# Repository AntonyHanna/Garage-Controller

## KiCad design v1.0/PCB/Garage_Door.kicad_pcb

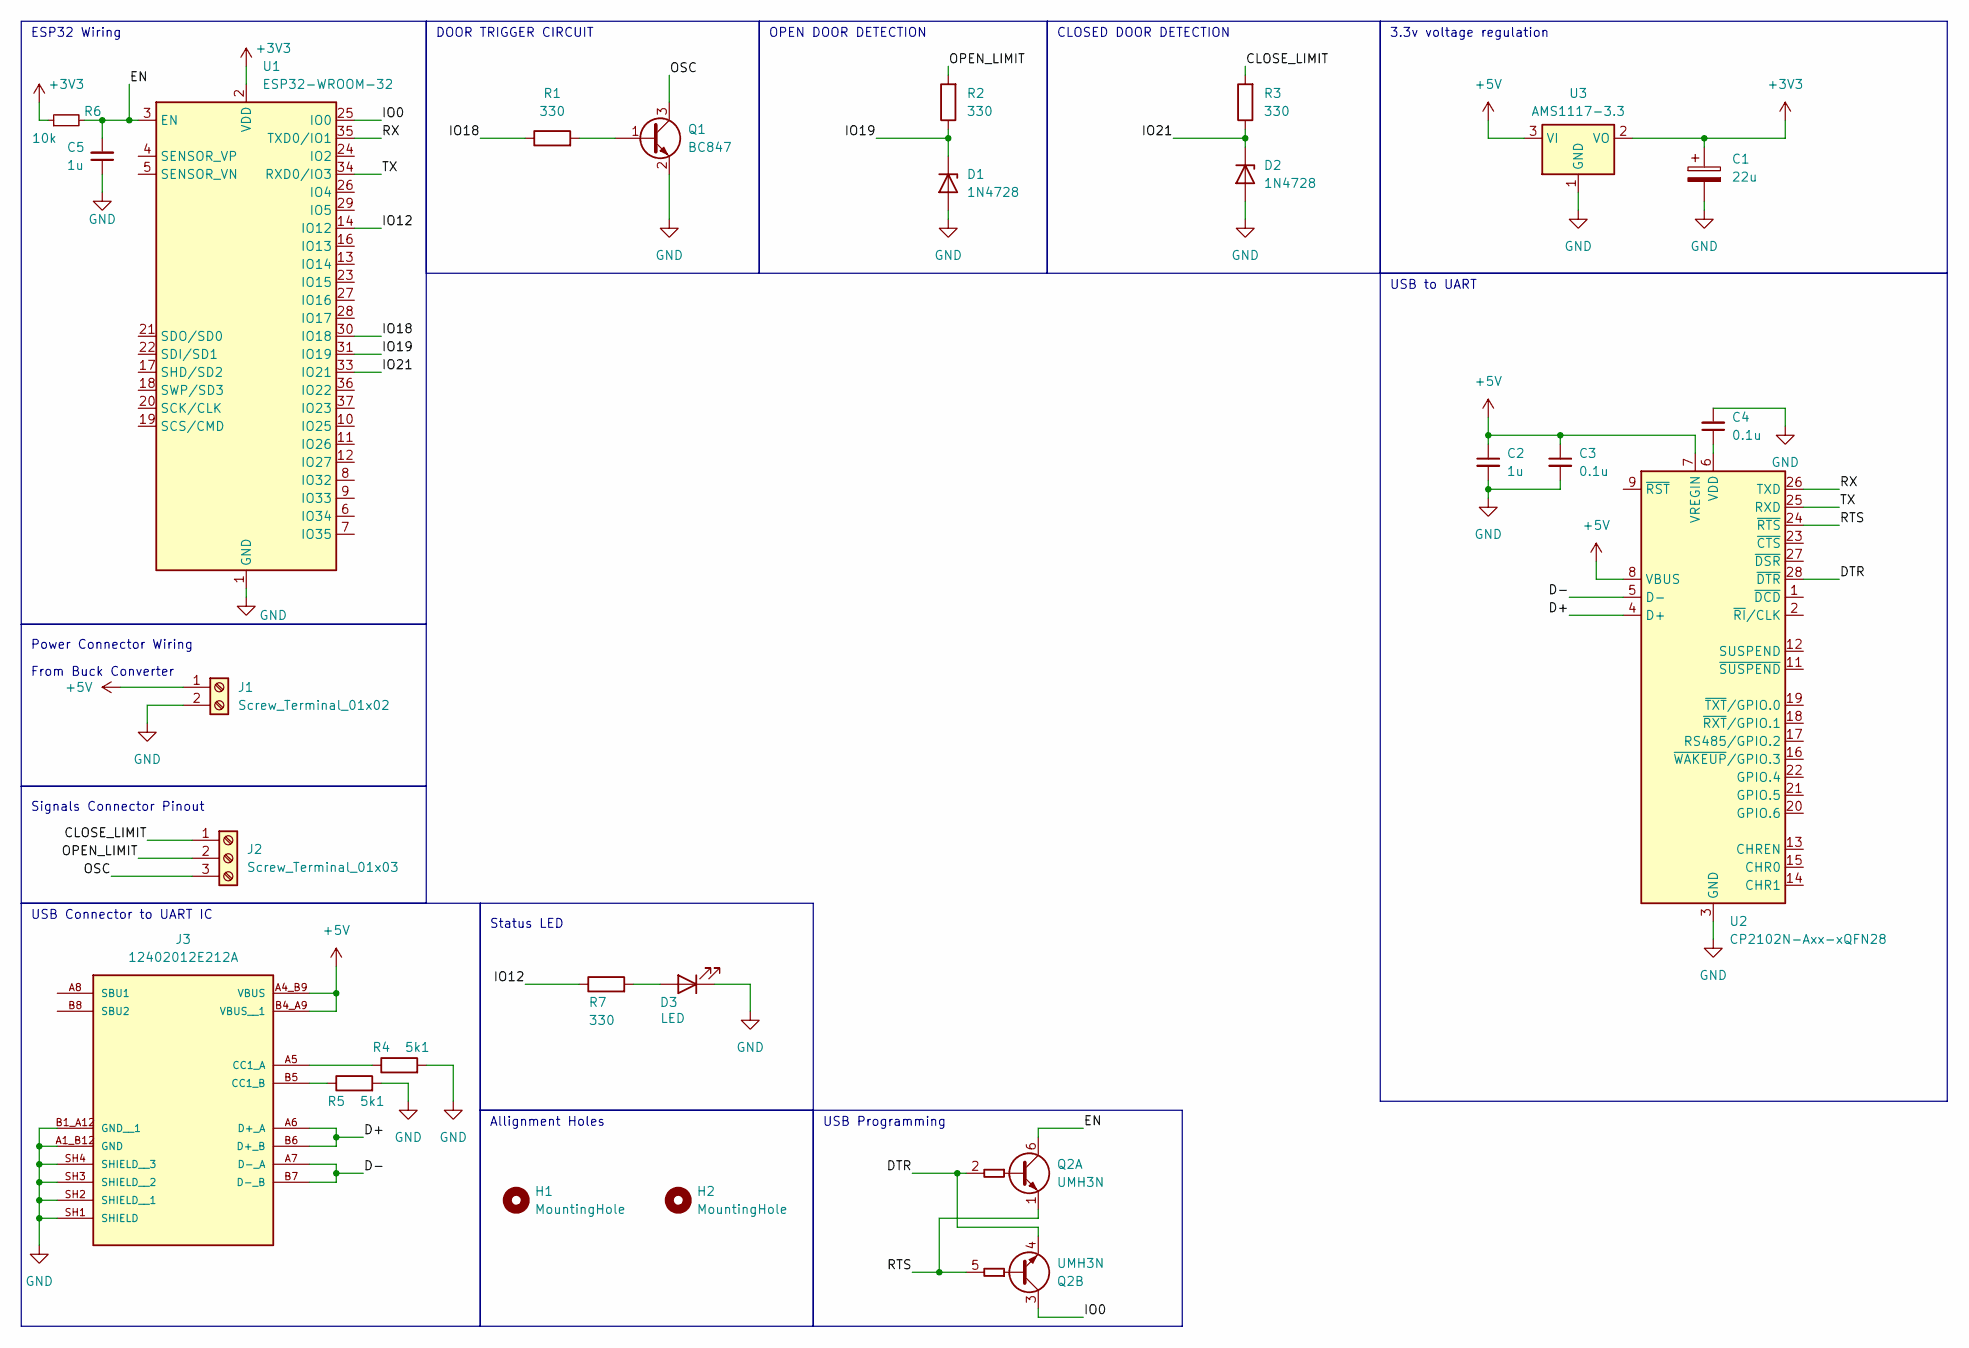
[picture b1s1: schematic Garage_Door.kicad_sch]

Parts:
C1: 22u; C_0603_1608Metric_Pad1.08x0.95mm_HandSolder
C2, C5: 1u; C_0603_1608Metric_Pad1.08x0.95mm_HandSolder
C3, C4: 0.1u; C_0603_1608Metric_Pad1.08x0.95mm_HandSolder
D1, D2: 1N4728; D_SOD-323F
D3: LED; LED_0603_1608Metric_Pad1.05x0.95mm_HandSolder
H1, H2: MountingHole; MountingHole_2.5mm
J1: Screw_Terminal_01x02; TerminalBlock_Phoenix_MKDS-1,5-2-5.08_1x02_P5.08mm_Horizont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
J2: Screw_Terminal_01x03; TerminalBlock_Phoenix_MKDS-1,5-3-5.08_1x03_P5.08mm_Horizont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
J3: 12402012E212A; AMPHENOL_12402012E212A; PARTREV 4
Q1: BC847; SOT-23
Q2: UMH3N; SOT-363_SC-70-6
R1, R2, R3, R7: 330; R_0603_1608Metric_Pad0.98x0.95mm_HandSolder
R4, R5: 5k1; R_0603_1608Metric_Pad0.98x0.95mm_HandSolder
R6: 10k; R_0603_1608Metric_Pad0.98x0.95mm_HandSolder
U1: ESP32-WROOM-32
U2: CP2102N-Axx-xQFN28; QFN-28-1EP_5x5mm_P0.5mm_EP3.35x3.35mm
U3: AMS1117-3.3; SOT-223-3_TabPin2

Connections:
+3V3: C1.1, R6.1, U1.2 (VDD), U3.2 (VO)
+5V: C2.1, C3.1, J1.1, J3.A4_B9 (VBUS), J3.B4_A9 (VBUS__1), U2.7 (VREGIN), U2.8 (VBUS), U3.3 (VI)
/CLOSE_LIMIT: J2.1, R3.2
/D+: J3.A6 (D+_A), J3.B6 (D+_B), U2.4 (D+)
/D-: J3.A7 (D-_A), J3.B7 (D-_B), U2.5 (D-)
/DTR: Q2.2 (B1), Q2.4 (E2), U2.28 (~DTR)
/EN: C5.2, Q2.6 (C1), R6.2, U1.3 (EN)
/IO0: Q2.3 (C2), U1.25 (IO0)
/IO12: R7.1, U1.14 (IO12)
/IO18: R1.1, U1.30 (IO18)
/IO19: D1.1 (K), R2.1, U1.31 (IO19)
/IO21: D2.1 (K), R3.1, U1.33 (IO21)
/OPEN_LIMIT: J2.2, R2.2
/OSC: J2.3, Q1.3 (C)
/RTS: Q2.1 (E1), Q2.5 (B2), U2.24 (~RTS)
/RX: U1.35 (TXD0/IO1), U2.26 (TXD)
/TX: U1.34 (RXD0/IO3), U2.25 (RXD)
GND: C1.2, C2.2, C3.2, C4.2, C5.1, D1.2 (A), D2.2 (A), D3.1 (K), J1.2, J3.A1_B12 (GND), J3.B1_A12 (GND__1), J3.SH1 (SHIELD), J3.SH2 (SHIELD__1), J3.SH3 (SHIELD__2), J3.SH4 (SHIELD__3), Q1.2 (E), R4.2, R5.2, U1.1 (GND), U1.15 (GND), U1.38 (GND), U1.39 (GND), U2.3 (GND), U2.29 (GND), U3.1 (GND)
unnamed: D3.2 (A), R7.2
unnamed: J3.A5 (CC1_A), R4.1
unnamed: J3.B5 (CC1_B), R5.1
unnamed: Q1.1 (B), R1.2
unnamed: C4.1, U2.6 (VDD)

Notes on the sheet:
Status LED
DOOR TRIGGER CIRCUIT
ESP32 Wiring
Allignment Holes
Signals Connector Pinout
From Buck Converter
CLOSED DOOR DETECTION
USB to UART
Power Connector Wiring
3.3v voltage regulation
USB Connector to UART IC
OPEN DOOR DETECTION
USB Programming

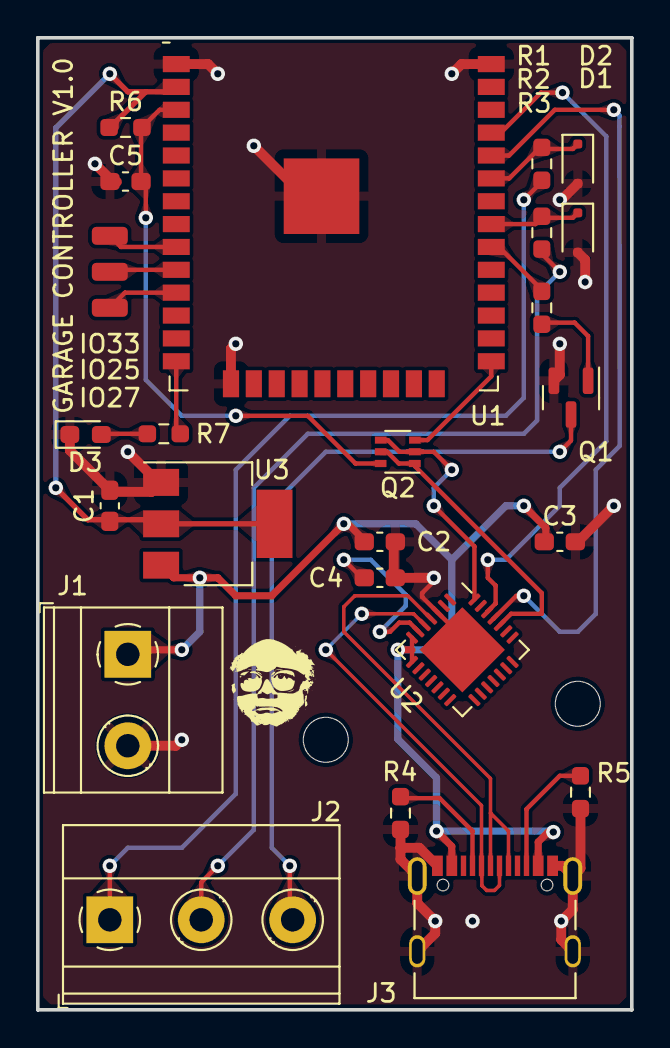
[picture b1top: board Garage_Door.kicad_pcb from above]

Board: 2 copper layers, 33.0 x 54.0 mm, 28 parts (0 on the bottom side), 23 nets.

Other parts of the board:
IO25, IO27, IO33: SolderWirePad_1x01_SMD_1x2mm

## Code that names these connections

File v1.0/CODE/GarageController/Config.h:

#define STATUS_LED 12

#define EXTRA_IO_1 33
#define EXTRA_IO_2 25
#define EXTRA_IO_3 26

#define CLOSE_LIMIT 21
#define OPEN_LIMIT 19
#define OSC 18

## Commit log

2024-02-12 Add v1.0 files
2024-02-13 Fixed: Null reference on unitialised characteristics Fixed services run in the wrong order Fixed invalid pinouts causing psram_init_fail
2024-02-16 General improvements
